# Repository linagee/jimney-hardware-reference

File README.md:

jimney-hardware-reference
===========================

Fork of pinoccio. Smaller, lighter, (faster?)

Contained are the schematics, board layout, data sheets, and BOM for the Jimney board.

The board revisions are also marked as tags in the git repository, if you'd like to see a previous version.

This is in Alpha right now, please don't produce any boards until you see this message go away.

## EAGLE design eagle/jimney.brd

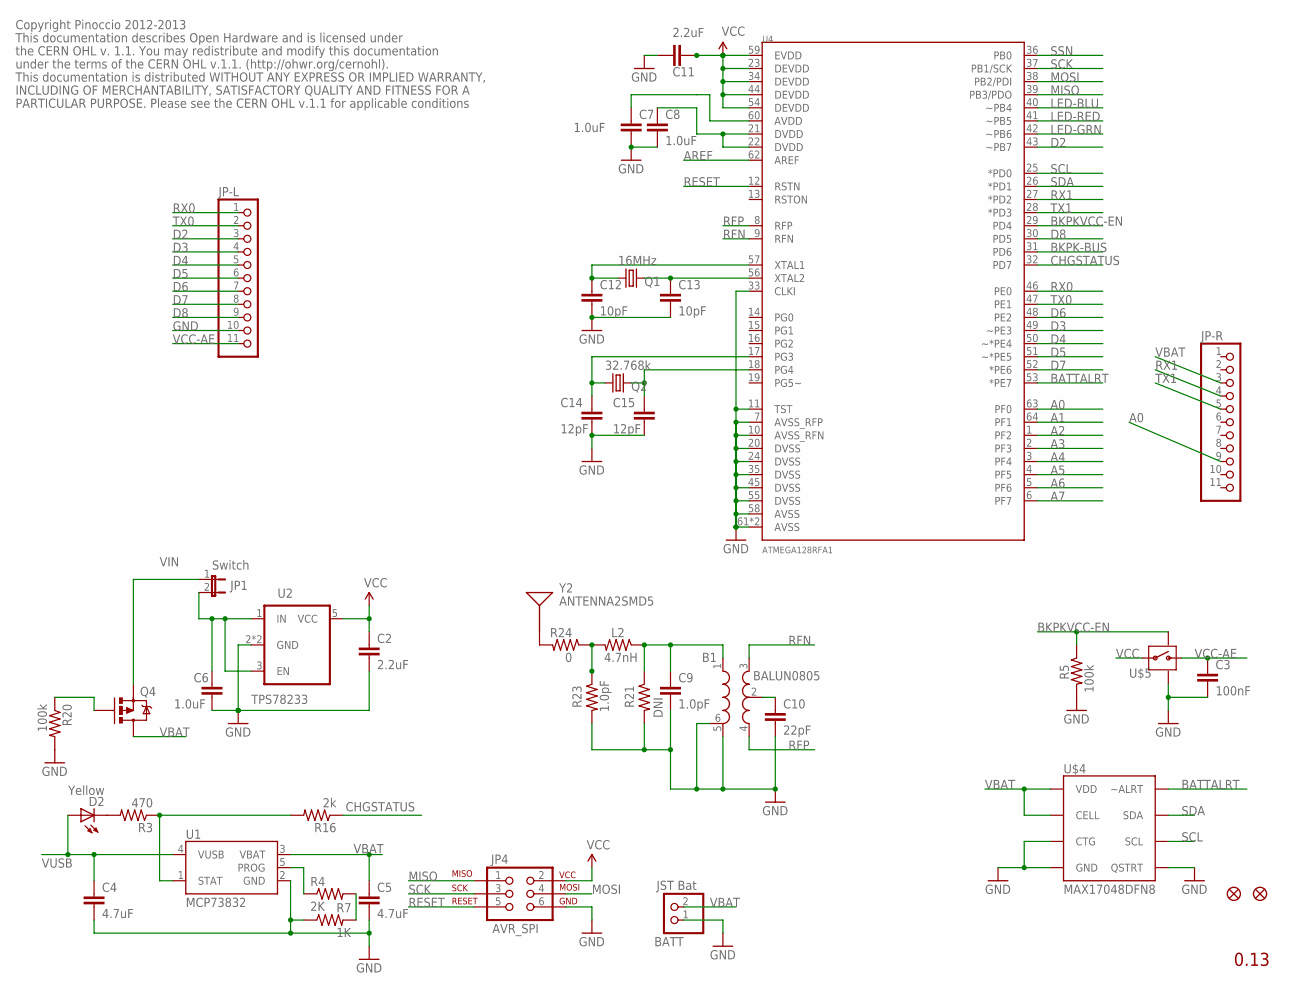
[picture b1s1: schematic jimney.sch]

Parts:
B1: BALUN0805; BALUN
BATT: JST Bat; 1X02
C2, C11: 2.2uF; 0402-CAP
C3: 100nF; 0402-CAP
C4, C5: 4.7uF; 0402-CAP
C6, C7, C8: 1.0uF; 0402-CAP
C9: 1.0pF; 0402-CAP
C10: 22pF; 0402-CAP
C12, C13: 10pF; 0402-CAP
C14, C15: 12pF; 0402-CAP
D2: Yellow; LED-0603
JP1: Switch; 1X02
JP3, JP5: FIDUCIAL1X2; FIDUCIAL-1X2
JP4: AVR_SPI; 2X3-PAD
JP-L: PINHD-1X11; 1X11
JP-R: PINHD-1X11; 1X11
L2: 4.7nH; 0402-RES
Q1: 16MHz; CRYSTAL-SMD-2.5X2-ABM10
Q2: 32.768k; CRYSTAL-SMD-2X1.2-ABS06
Q4: MOSFET-PCHANNELSMD; SOT23-3
R3: 470; 0402-RES
R4: 2K; 0402-RES
R5, R20: 100k; 0402-RES
R7: 1K; 0402-RES
R16: 2k; 0402-RES
R21: DNI; 0402-RES
R23: 1.0pF; 0402-RES
R24: 0; 0402-RES
U1: MCP73832; SOT23-5
U2: TPS78233; SOT23-5
U4: ATMEGA128RFA1; QFN-64
U$4: MAX17048DFN8; DFN-8
U$5: SWITCH-MOSFETTDFN4; TDFN4
Y2: ANTENNA2SMD5; ANTENNA-CHIP5

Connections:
A0: JP-R.9, U4.63 (PF0)
A1: U4.64 (PF1)
A2: U4.1 (PF2)
A3: U4.2 (PF3)
A4: U4.3 (PF4)
A5: U4.4 (PF5)
A6: U4.5 (PF6)
A7: U4.6 (PF7)
AREF: U4.62 (AREF)
BATTALRT: U4.53 (*PE7), U$4.P$5 (~ALRT)
BKPK-BUS: U4.31 (PD6)
BKPKVCC-EN: R5.1, U4.29 (PD4), U$5.P$4 (ON)
CHGSTATUS: R16.1, U4.32 (PD7)
D2: U4.43 (~PB7)
D3: U4.49 (~PE3)
D4: U4.50 (~*PE4)
D5: U4.51 (~*PE5)
D6: U4.48 (PE2)
D7: U4.52 (*PE6)
D8: U4.30 (PD5)
GND: B1.5 (GND), B1.6 (GND), BATT.1, C2.2, C3.2, C4.2, C5.2, C6.2, C7.2, C8.2, C9.2, C10.2, C11.2, C12.2, C13.2, C14.2, C15.2, JP4.6, R5.2, R7.1, R20.2, R21.2, R23.2, U1.2 (GND), U2.2 (GND), U2.4 (GND), U4.7 (AVSS_RFP), U4.10 (AVSS_RFN), U4.11 (TST), U4.20 (DVSS), U4.24 (DVSS), U4.33 (CLKI), U4.35 (DVSS), U4.45 (DVSS), U4.55 (DVSS), U4.58 (AVSS), U4.61 (AVSS), U4.PADDLE (AVSS), U$4.P$1 (CTG), U$4.P$4 (GND), U$4.P$6 (QSTRT), U$4.P$9 (GND), U$5.P$2 (GND), U$5.P$5 (GND)
LED-BLU: U4.40 (~PB4)
LED-GRN: U4.42 (~PB6)
LED-RED: U4.41 (~PB5)
MISO: JP4.1, U4.39 (PB3/PDO)
MOSI: JP4.4, U4.38 (PB2/PDI)
unnamed: B1.1 (IN), C9.1, L2.1, R21.1
unnamed: R4.2, R7.2
unnamed: C7.1, U4.60 (AVDD)
unnamed: R3.1, R16.2, U1.1 (STAT)
unnamed: B1.2 (RFGND), C10.1
unnamed: C12.1, Q1.P$1 (1), U4.57 (XTAL1)
unnamed: C13.1, Q1.P$3 (2), U4.56 (XTAL2)
unnamed: C14.1, Q2.P$1 (1), U4.17 (PG3)
unnamed: C15.1, Q2.P$2 (2), U4.18 (PG4)
unnamed: C8.1, U4.21 (DVDD), U4.22 (DVDD)
unnamed: D2.C, R3.2
unnamed: L2.2, R23.1, R24.1
unnamed: R24.2, Y2.FEED
unnamed: JP1.1, Q4.2 (S)
PROG: R4.1, U1.5 (PROG)
RESET: JP4.5, U4.12 (RSTN)
RFN: B1.3 (OUT1), U4.9 (RFN)
RFP: B1.4 (OUT2), U4.8 (RFP)
RX0: U4.46 (PE0)
RX1: JP-R.4, U4.27 (*PD2)
SCK: JP4.3, U4.37 (PB1/SCK)
SCL: U4.25 (*PD0), U$4.P$7 (SCL)
SDA: U4.26 (*PD1), U$4.P$8 (SDA)
SSN: U4.36 (PB0)
TX0: U4.47 (PE1)
TX1: JP-R.5, U4.28 (*PD3)
VBAT: BATT.2, C5.1, JP-R.3, Q4.3 (D), U1.3 (VBAT), U$4.P$2 (CELL), U$4.P$3 (VDD)
VCC: C2.1, C11.1, JP4.2, U2.5 (VCC), U4.23 (DEVDD), U4.34 (DEVDD), U4.44 (DEVDD), U4.54 (DEVDD), U4.59 (EVDD), U$5.P$3 (IN)
VCC-AE: C3.1, U$5.P$1 (OUT)
VIN: C6.1, JP1.2, U2.1 (IN), U2.3 (EN)
VUSB: C4.1, D2.A, Q4.1 (G), R20.1, U1.4 (VUSB)

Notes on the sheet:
0.13
Copyright Pinoccio 2012-2013
This documentation describes Open Hardware and is licensed under
the CERN OHL v. 1.1. You may redistribute and modify this documentation
under the terms of the CERN OHL v.1.1. (http://ohwr.org/cernohl).
This documentation is distributed WITHOUT ANY EXPRESS OR IMPLIED WARRANTY,
INCLUDING OF MERCHANTABILITY, SATISFACTORY QUALITY AND FITNESS FOR A
PARTICULAR PURPOSE. Please see the CERN OHL v.1.1 for applicable conditions

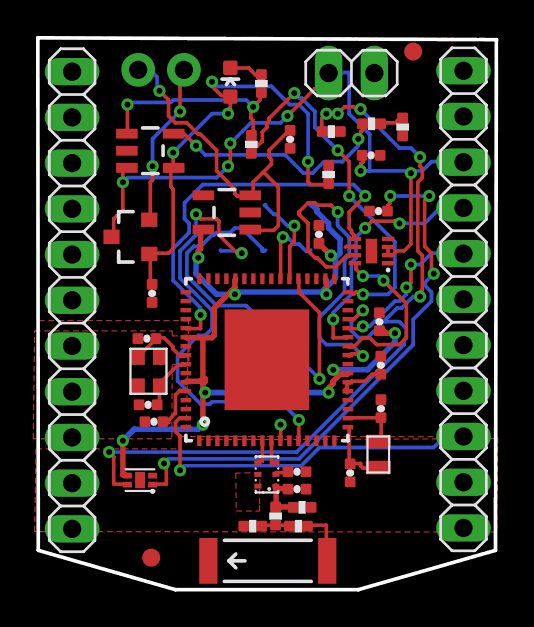
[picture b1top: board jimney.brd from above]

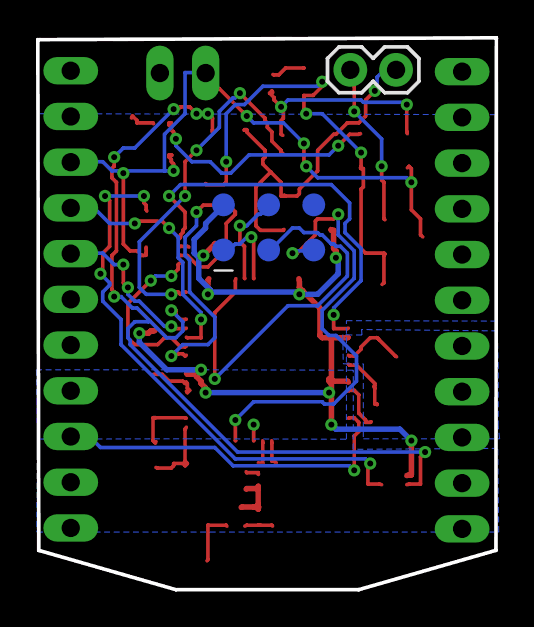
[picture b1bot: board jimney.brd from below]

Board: 2 copper layers, 25.5 x 30.7 mm, 42 parts (2 on the bottom side), 35 nets.

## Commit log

2013-07-18 Deleting pinoccio pdfs
2013-07-18 adding some readme
2013-07-18 Just a test, not all wires routed yet.

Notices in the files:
eagle/jimney.brd:
Licensed under CERN OHL v.1.1
parts and their libraries:
BeanLabs: Licensing: CC v3.0 Share-Alike You are welcome to use this library for commercial purposes.
